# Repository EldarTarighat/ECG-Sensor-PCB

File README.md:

# ECG-Sensor-PCB
A compact, open-source hardware module for ECG (Electrocardiogram) signal acquisition. This project includes the complete KiCad PCB design files and the LTspice simulation for the analog front-end. The board is designed with through-hole components for easy hand-soldering.

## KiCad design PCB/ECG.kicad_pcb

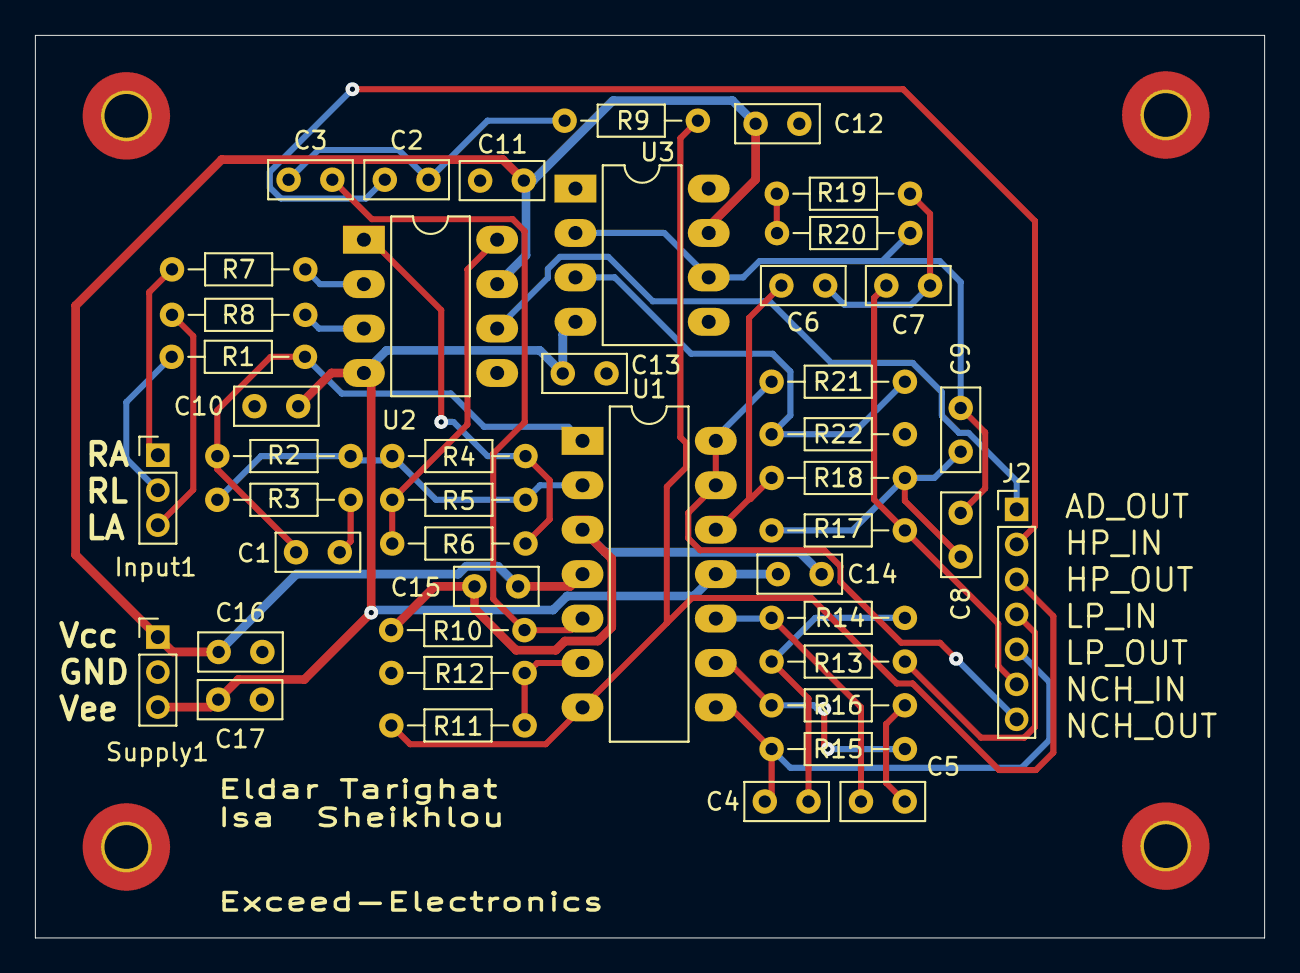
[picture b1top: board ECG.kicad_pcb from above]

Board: 2 copper layers, 70.3 x 51.6 mm, 45 parts (0 on the bottom side), 32 nets.

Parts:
C1, C2, C3, C4, C5, C6, C7, C8, C9, C10, C11, C12, C13, C14, C15, C16, C17: C; C_Rect_L4.6mm_W2.0mm_P2.50mm_MKS02_FKP02
Input1: Conn_01x03_Pin; PinHeader_1x03_P2.00mm_Vertical
J2: Conn_01x07_Pin; PinHeader_1x07_P2.00mm_Vertical
R1, R2, R3, R4, R5, R6, R7, R8, R9, R10, R11, R12, R13, R14, R15, R16, R17, R18, R19, R20, R21, R22: R; R_Axial_DIN0204_L3.6mm_D1.6mm_P7.62mm_Horizontal
Supply1: Conn_01x03_Pin; PinHeader_1x03_P2.00mm_Vertical
U1: TL084; CERDIP-14_W7.62mm_SideBrazed_LongPads
U2: AD620; DIP-8_W7.62mm_LongPads
U3: TL081; DIP-8_W7.62mm_LongPads

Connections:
GND: C5.2, C10.2, C11.2, C12.2, C13.1, C14.1, C15.2, C16.2, C17.1, R10.1, R12.2, R16.2, R22.2, Supply1.2, U1.3 (+), U2.5 (Ref)
unnamed: C1.1, R1.1, R2.1, U1.1
unnamed: C1.2, R3.1
unnamed: C2.2, C3.1, R9.1
unnamed: C4.2, R13.1, R14.2
unnamed: C6.2, C7.1, R19.1
unnamed: C8.1, C9.1, R17.1, R18.2
unnamed: Input1.1, R7.2
unnamed: Input1.2, R1.2
unnamed: Input1.3, R8.1
unnamed: J2.1, U2.6
unnamed: C2.1, J2.2
unnamed: J2.3, R9.2, R11.1, U1.7
unnamed: J2.4, R13.2
unnamed: C4.1, J2.5, R15.1, U1.8
unnamed: C7.2, J2.6, R17.2
unnamed: J2.7, R21.1, U1.13 (-), U1.14
unnamed: R4.2, R6.2, U2.1 (Rg)
unnamed: R5.1, R6.1, U2.8 (Rg)
unnamed: R19.2, R20.1
unnamed: C11.1, C12.1, C15.1, C16.1, Supply1.1, U1.4 (V+), U2.7 (Vs+), U3.7 (V+)
unnamed: C10.1, C13.2, C14.2, C17.2, Supply1.3, U1.11 (V-), U2.4 (Vs-), U3.4 (V-)
unnamed: R2.2, R3.2, R4.1, R5.2, U1.2 (-)
unnamed: C3.2, R10.2, U1.5 (+)
unnamed: R11.2, R12.1, U1.6 (-)
unnamed: C5.1, R14.1, U1.10 (+)
unnamed: R15.2, R16.1, U1.9 (-)
unnamed: C6.1, R18.1, U1.12 (+)
unnamed: R8.2, U2.3 (+)
unnamed: R7.1, U2.2 (-)
unnamed: R21.2, R22.1, U3.3 (+)
unnamed: C8.2, C9.2, R20.2, U3.2 (-), U3.6

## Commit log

2025-10-16 Add initial KiCad project files
